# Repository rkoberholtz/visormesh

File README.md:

# VisorMesh

A MeshCore client for the Handspring Visor (Palm OS 3.5.2H3.0).

The Visor works as a terminal for a MeshCore **companion radio**. The radio (a Seeed XIAO nRF52840 with a Wio-SX1262) handles LoRa, routing and crypto. The Visor only speaks the companion framing protocol over a byte stream. The radio sits on a custom Springboard module with its own LiPo, so it keeps meshing while the Visor sleeps.

See [docs/design.md](docs/design.md) for the architecture and the reasons behind each decision, and [docs/progress.md](docs/progress.md) for the current status and log.

## Repo layout

| Path | What |
|---|---|
| `hardware/sb-lora/` | SB-LoRa Springboard carrier board: KiCad, fab outputs (JLCPCB), generator scripts. See its [README](hardware/sb-lora/README.md) |
| `firmware/` | MeshCore companion firmware patch for the XIAO (UART on D6/D7 plus USB), build Makefile, bench query tool and a fake radio |
| `palm-client/` | VisorMesh, the Palm OS client: MeshTerm-style conversations, channels, contacts, node settings. Works over the Visor USB cradle via a Mac bridge until the SB-LoRa boards arrive. See its [README](palm-client/README.md) |
| `docs/design.md` | Architecture, protocol notes and decisions |
| `docs/progress.md` | Status, milestones and a dated log |
| `docs/upstream-issues.md` | Problems found in pilot-link, PilRC/prc-tools and MeshCore, with evidence and workarounds, ready to report |
| `docs/reference/` | Third-party reference: Handspring Springboard dev guide and mechanical spec, the Handspring SDK (`HsExt.h`, Springboard docs and tools), springSD v1.1 hardware |

## Versioning

Hardware revisions are tagged in git (`hw-v0.1`, `hw-v0.2`, ...), so the files that went to fab for each order stay recoverable. Each board's README records its revision and status.

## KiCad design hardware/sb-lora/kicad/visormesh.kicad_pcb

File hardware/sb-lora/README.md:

# VisorMesh SB-LoRa v0.1

A Springboard module for the Handspring Visor that carries a Seeed XIAO nRF52840 + Wio-SX1262 stack running MeshCore companion firmware. The Visor talks to it over a bit-banged SPI link into an SC16IS740 UART bridge. The XIAO runs from its own LiPo and keeps meshing while the Visor sleeps or the module is unplugged.

**Status: prototype design, not yet built.** DRC is clean (0 unconnected pads) and the netlist was cross-checked against the Springboard Development Guide pin table, the SC16IS740 datasheet pinout, and Dmitry Grinberg's springSD v1.1 connector footprint. Order 5 boards and build one before trusting it.

## What's in here

| Path | What |
|---|---|
| `fab/visormesh_gerbers_jlcpcb.zip` | Gerbers + Excellon drill, upload as-is to JLCPCB or PCBWay |
| `fab/visormesh_bom_jlcpcb.csv` | BOM, JLC format (LCSC part numbers) |
| `fab/visormesh_cpl_jlcpcb.csv` | Pick-and-place, JLC format, top side only |
| `fab/hand_fit_parts.csv` | Parts you fit yourself (J1, J2, J3, JP1) |
| `fab/visormesh_schematic.pdf` | Net-label schematic + theory of operation |
| `fab/visormesh_assembly_top.pdf` | Assembly drawing with reference designators |
| `kicad/` | KiCad 7 board + project + custom DRC rule (opens in KiCad 7 or 8) |
| `source/` | The scripts that generated everything. `netlist.py` is the single source of truth |
| `../../firmware/` | MeshCore patch: `Xiao_nrf52_companion_radio_uart` env (companion protocol on D6/D7) |
| `renders/` | Top and bottom copper renders |

## Ordering (JLCPCB)

- PCB: 2 layers, **1.6 mm**, 1 oz, any color. **ENIG recommended** (flat pads for the 0.65 mm TSSOP, SC-70 parts and the straddle connector); lead-free HASL works too.
- Board is 50.43 x 75.15 mm. The bottom 50.47 mm is the in-slot section, using springSD's exact outline. The top 24.6 mm sticks out of the Visor and carries the XIAO stack.
- Assembly: top side, Economic PCBA is fine. Upload BOM + CPL. **Check part rotations in JLC's placement preview** before paying, especially U1-U7, Y1 and D1; KiCad and JLC disagree on rotation for some SOT/SC-70 footprints. Pin 1 of each IC is marked on the silkscreen and assembly drawing. The CPL already includes the corrections found in the first order's preview (U1, U2, U4 at 270; U3, U5-U7 at 180), so the dots should land on the pin-1 triangles without adjustment. Still glance at the preview: JLC can change its part models.
- Extended parts: SC16IS740 (C407851), 74LVC1G80 (C353857), crystal (C2901666) and probably the SN74LVC1T45 (C9382) and 74LVC1G04 (C10237). Expect extended-part loading fees.

## Parts you fit by hand

1. **J1 Springboard connector**: Hirose **IC1HA-68RD-1.27SH(51)**, the PC-Card-style straddle receptacle springSD uses. It clamps the board edge; pins 1-34 land on the top pads, 35-68 on the bottom.
   - **Obsolete** (no longer stocked at DigiKey or Mouser as of Nov 2026). Sources: new-old stock on eBay or brokers (search Octopart for the exact part number with the `(51)` suffix; about $24 each), or harvest one from a used Springboard module.
   - The Springboard connector core is a standard PCMCIA 68-pin connector with different housing keying (Dev Guide §5, §7.1). Handspring used four board-offset variants (−0.3, 0, +0.3, +0.6 mm); a harvested connector's offset sets how high the board sits in the slot, so compare it against a (51) or dry-fit before soldering.
   - An earlier note here suggested XKB X1321FV-2x34 (LCSC C2881777) as a substitute. That was never verified: the closest LCSC listing (X1321FVS-2x34, C2881881) is a vertical SMD socket, not an edge straddle, and won't fit this footprint.
   - Pin 1 is marked on silk at the right-hand end of the top row.
2. **J2/J3**: two 1x7 2.54 mm female headers (low-profile if you can find them). Your XIAO+Wio stack plugs in here. You can also solder the stack's pins straight into the holes.
3. **JP1**: leave **open**. See VDOCK below.

## Mechanical / orientation

- The XIAO sits with **components facing up (same side as U1-U7) and USB-C at the outer edge**. Silkscreen labels (D0..D6, 5V, GND, 3V3, D10..D7) show which header pin goes where. **Check them against your stack before plugging in.** If your stack only exposes pins upside-down, the labels tell you it's mirrored.
- Solder your LiPo to the XIAO's BAT+/BAT- pads first. The carrier doesn't touch the battery; the XIAO's own charger handles it over USB-C.
- In-slot components are all 1.25 mm or shorter, on the top side only, which is lower than springSD's microSD socket. The bottom side inside the slot is a flat GND pour.
- **Assumption to verify:** like springSD, the top edge of the 50.47 mm section lines up with the slot opening, and the extension (with the stack and antenna) protrudes like a battery-module bump. Dry-fit a bare board before soldering anything.

## Electrical summary

- **Bus SPI** (same wiring as springSD, so its 68k routines port directly):
  - A CS0* access latches A17 and A8 on its rising edge. Through Q-bar, `nCS = NOT A17` and `MOSI = NOT A8`.
  - A CS1* read produces one SCLK pulse; MISO comes back on D0 through a 1k resistor.
  - SC16IS740 is SPI mode 0. Register byte: bit7 = R/W (1 = read), bits 6:3 = register, bits 2:1 = channel 00.
- **UART**: 14.7456 MHz crystal (SCTF SX3B14.7456F2010F30, 20 pF load; replaced the out-of-stock SXT32413BA07 rated 13 pF), so 115200 baud with DLL=8, DLH=0 (prescaler 1). 64-byte TX/RX FIFOs. IRQ* goes straight to the Springboard IRQ* (the Visor has the pull-up). RESET* follows the slot RESET*.
- **Power isolation**: only U5-U7 (SN74LVC1T45) touch both domains, and both of their ports go Hi-Z when either supply is 0 V. Removing the module, a LOWBAT power cut, or a flat LiPo can't back-power the other side.
- **Visor-present**: XIAO D0 is high when the slot is powered. The firmware can stop pushing frames when it's low; the companion queues messages anyway.
- **Slot budget**: a few mA active, against the 100 mA limit. To stay inside the 100 uA standby limit, put the SC16IS740 to sleep (IER bit 4) when the Palm app is idle.
- **VDOCK (JP1)**: when bridged, VDOCK (4.75-6.2 V, only present in a charging dock) feeds the XIAO 5V pin through a Schottky so the XIAO charger can top up the LiPo while docked. The standard Visor USB cradle almost certainly doesn't supply VDOCK on an AAA Visor. **If you bridge JP1, never plug USB-C in while docked**, because VDOCK would back-feed the USB host.

## Bring-up order

[BRINGUP.md](BRINGUP.md) has the full plan: checks and expected readings for each step, and what each line of the Visor's SB-LoRa Test means. In short:

1. Bare board, before soldering anything: check continuity of VSB (J1 pins 17/51) and GND, then dry-fit in the Visor slot.
2. After JLC assembly, fit J1 only. Bench-power VSB at 3.3 V through a current-limited supply. Expect a few mA, and the crystal at 14.7456 MHz on Y1.
3. Insert into the Visor with nothing on J2/J3. Port springSD's bus routines and read the SC16IS740 scratch register (SPR, reg 0x07): write and read back a pattern. That proves the CS0/CS1 latch path.
4. Flash the XIAO with `Xiao_nrf52_companion_radio_uart` (patch in `../../firmware/`). Bench-test it over a 3.3 V USB-TTL adapter on D6/D7 with meshcore-cli before plugging the stack into the carrier.
5. Plug in the stack. Configure the SC16IS740 for 115200 8N1, send CMD_DEVICE_QUERY (`<` + len + `0x16 0x03`), and look for a `>`-framed DEVICE_INFO reply.

## Known limits / things I could not verify from here

- Mechanical fit of the extension against the Visor body and the exact slot depth (see the assumption above).
- The J1 footprint is copied pad-for-pad from springSD v1.1 (verified against its IPC-356 netlist). I could not check it against the Hirose drawing.
- JLC part rotations (see Ordering).
- There is no `.kicad_sch`: the schematic is generated from `source/netlist.py` as a PDF, and the board's nets come from the same file. To regenerate on a machine with KiCad 7, Java and Freerouting 2.1: `source/make.sh` (autoroutes), then `make_fab.py`, `verify.py`, `draw_schematic.py`. Routing is nondeterministic between runs.

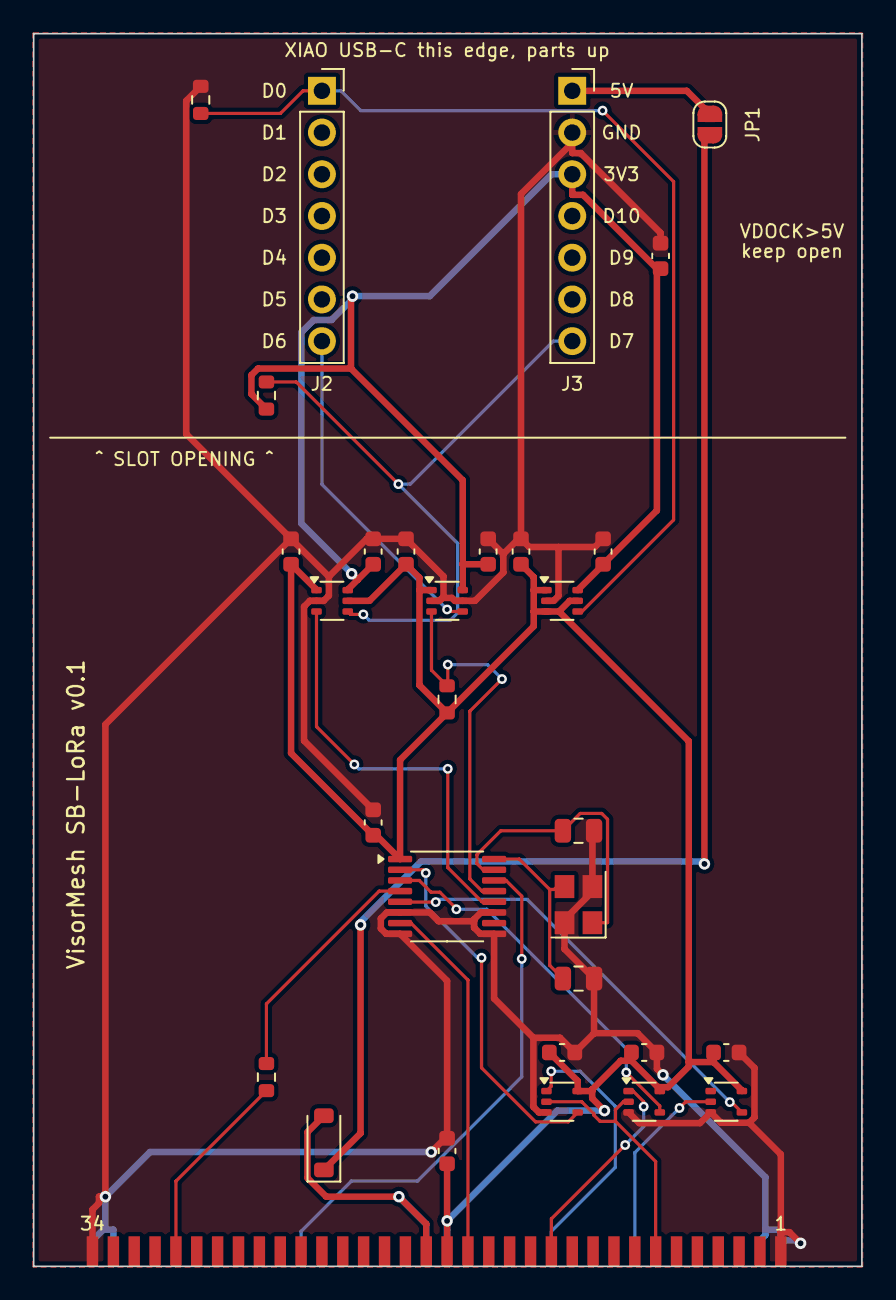
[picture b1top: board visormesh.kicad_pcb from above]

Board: 2 copper layers, 50.4 x 75.1 mm, 31 parts (0 on the bottom side), 24 nets.

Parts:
C1, C14: 1uF; C_0603_1608Metric
C2, C3, C4, C5, C8, C9, C10, C11, C12, C13: 100nF; C_0603_1608Metric
C6, C7: 22pF C0G; C_0805_2012Metric
D1: B5819W; D_SOD-123
J1: Springboard 68p; SPRINGBOARD_68_STRADDLE
J2: XIAO left 1x7; PinSocket_1x07_P2.54mm_Vertical
J3: XIAO right 1x7; PinSocket_1x07_P2.54mm_Vertical
JP1: VDOCK EN; SolderJumper-2_P1.3mm_Open_RoundedPad1.0x1.5mm
R1: 1k; R_0603_1608Metric
R2, R3, R4: 100k; R_0603_1608Metric
U1, U2: 74LVC1G80GW; SOT-353_SC-70-5
U3: 74LVC1G04GW; SOT-353_SC-70-5
U4: SC16IS740IPW; TSSOP-16_4.4x5mm_P0.65mm
U5, U6, U7: SN74LVC1T45DCKR; SOT-363_SC-70-6
Y1: 14.7456MHz 20pF; Crystal_SMD_3225-4Pin_3.2x2.5mm

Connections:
3V3X: C9.1, C11.1, C13.1, C14.1, J3.3, R2.1, U5.6, U6.6, U7.6
A8: J1.12, U2.1
A17: J1.46, U1.1
BR_RX: R3.2, U4.13, U6.3
BR_TX: U4.12, U5.3
CS0_N: J1.7, U1.2, U2.2
CS1_N: J1.42, U3.2
D0: J1.30, R1.1
GND: C1.2, C2.2, C3.2, C4.2, C5.2, C6.2, C7.2, C8.2, C9.2, C10.2, C11.2, C12.2, C13.2, C14.2, J1.1, J1.34, J1.35, J1.36, J1.67, J1.68, J3.2, R4.2, U1.3, U2.3, U3.3, U4.6, U4.8, U4.9, U4.11, U5.2, U6.2, U6.5, U7.2, Y1.2, Y1.4
IRQ_N: J1.16, U4.7
RESET_N: J1.58, U4.14
SPI_MISO: R1.2, U4.4
SPI_MOSI: U2.4, U4.3
SPI_NCS: U1.4, U4.2
SPI_SCLK: U3.4, U4.5
VDOCK: D1.2, J1.18, J1.52
VDOCK_D: D1.1, JP1.1
VISOR_PRESENT: J2.1, R4.1, U7.4
VSB: C1.1, C2.1, C3.1, C4.1, C5.1, C8.1, C10.1, C12.1, J1.17, J1.51, R3.1, U1.5, U2.5, U3.5, U4.1, U5.1, U5.5, U6.1, U7.1, U7.3, U7.5
XIAO_RX: J3.7, R2.2, U5.4
XIAO_TX: J2.7, U6.4
XIAO_VBUS: J3.1, JP1.2
XTAL1: C6.1, U4.15, Y1.1
XTAL2: C7.1, U4.16, Y1.3

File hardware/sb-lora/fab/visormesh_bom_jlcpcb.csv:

Comment,Designator,Footprint,LCSC Part #
1uF,"C1,C14",C_0603_1608Metric,C15849
100nF,"C2,C3,C4,C5,C8,C9,C10,C11,C12,C13",C_0603_1608Metric,C14663
22pF C0G,"C6,C7",C_0805_2012Metric,C24658
B5819W,D1,D_SOD-123,C8598
1k,R1,R_0603_1608Metric,C21190
100k,"R2,R3,R4",R_0603_1608Metric,C25803
74LVC1G80GW,"U1,U2",SOT-353_SC-70-5,C353857
74LVC1G04GW,U3,SOT-353_SC-70-5,C10237
SC16IS740IPW,U4,TSSOP-16_4.4x5mm_P0.65mm,C407851
SN74LVC1T45DCKR,"U5,U6,U7",SOT-363_SC-70-6,C9382
14.7456MHz 20pF,Y1,Crystal_SMD_3225-4Pin_3.2x2.5mm,C2901666
